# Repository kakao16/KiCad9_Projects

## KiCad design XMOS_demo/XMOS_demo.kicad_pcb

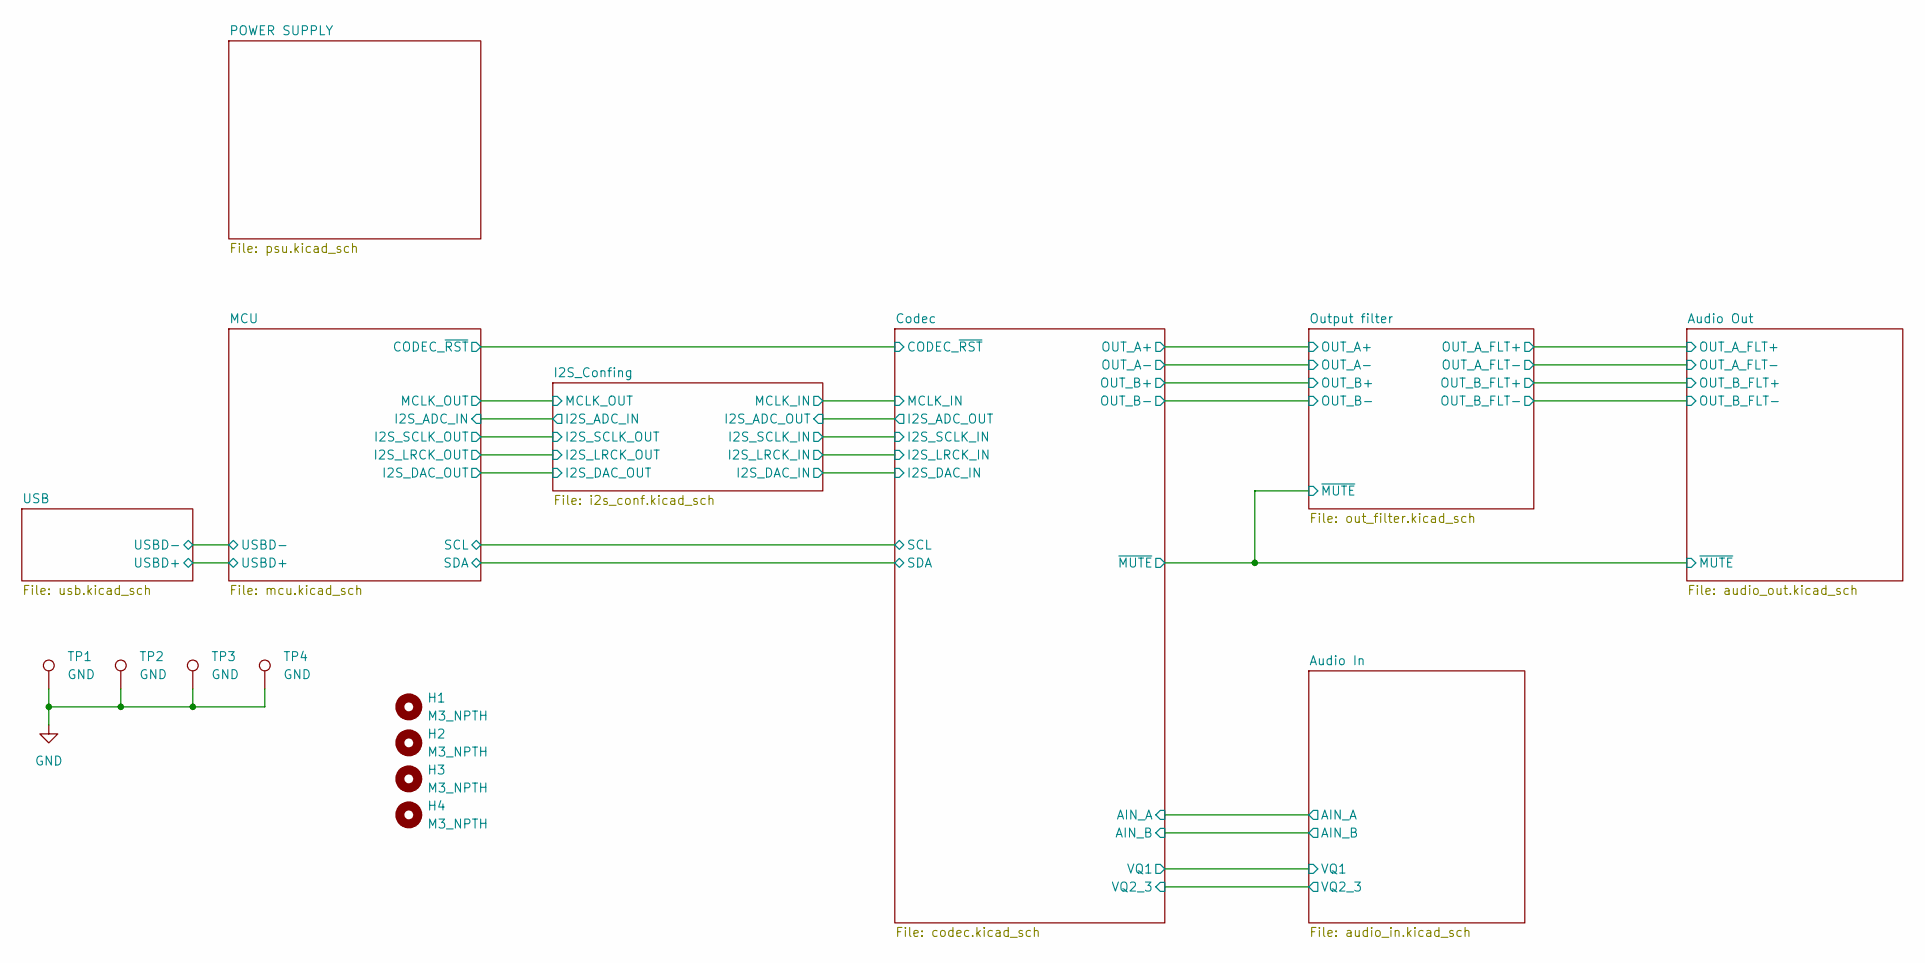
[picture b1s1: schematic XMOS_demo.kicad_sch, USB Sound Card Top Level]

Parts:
H1, H2, H3, H4: M3_NPTH; MountingHole_3.2mm_M3
TP1, TP2, TP3, TP4: GND; TestPoint_Bridge_Pitch2.54mm_Drill1.0mm

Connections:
GND: TP1.1, TP2.1, TP3.1, TP4.1; also elsewhere on the board

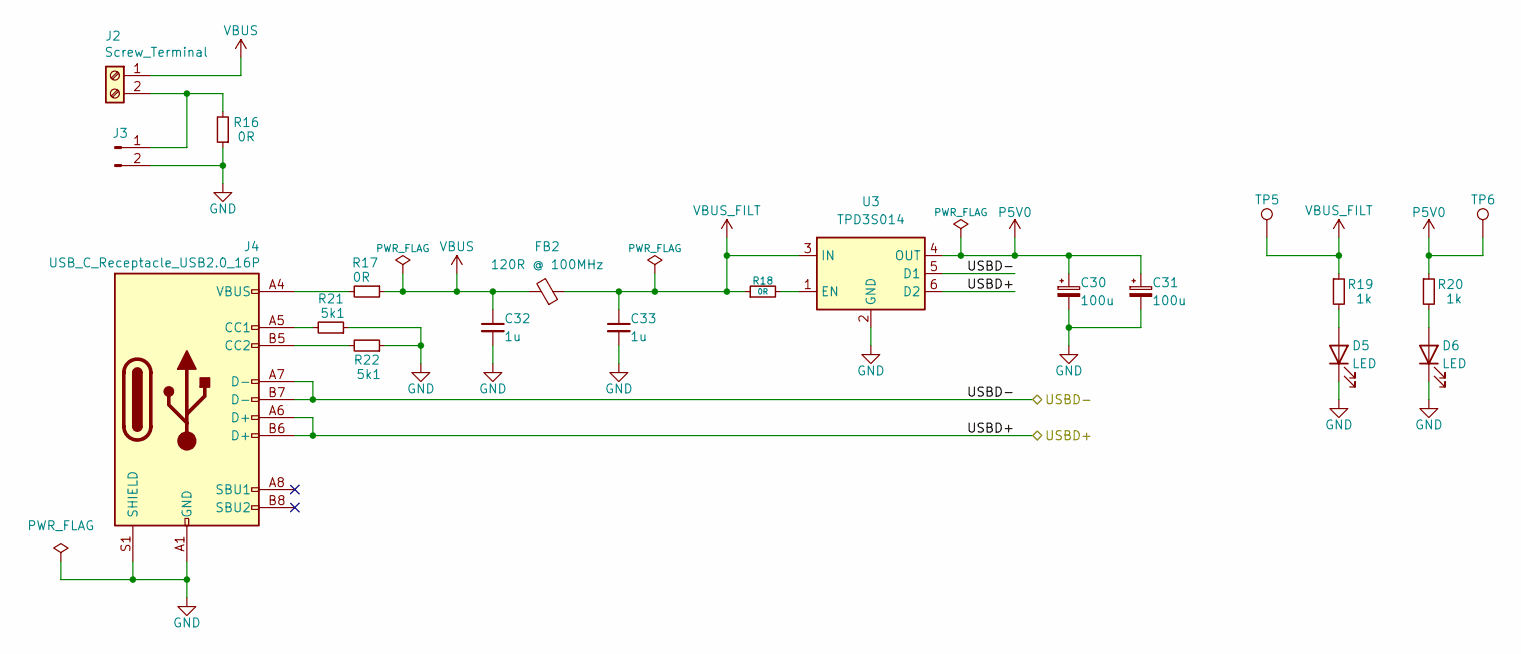
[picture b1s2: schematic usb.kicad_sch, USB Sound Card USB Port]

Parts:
C30, C31: 100u; CP_Elec_6.3x5.7
C32, C33: 1u; C_0603_1608Metric; Max Voltage 16V
D5, D6: LED; LED_0603_1608Metric
FB2: 120R @ 100MHz; L_0603_1608Metric; MPN MI0603M121R-10
J2: Screw_Terminal; TerminalBlock_Phoenix_PT-1,5-2-3.5-H_1x02_P3.50mm_Horizontal
J3: Conn_01x02_Pin; PinHeader_1x02_P2.54mm_Vertical
J4: USB_C_Receptacle_USB2.0_16P; USB_C_Receptacle_GCT_USB4085
R16, R17, R18: 0R; R_0603_1608Metric
R19, R20: 1k; R_0603_1608Metric
R21, R22: 5k1; R_0603_1608Metric
TP5, TP6: TestPoint; TestPoint_Keystone_5005-5009_Compact
U3: TPD3S014; SOT-23-6; MPN TPD3S014DBVR

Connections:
/USB/USBD+: J4.A6 (D+), J4.B6 (D+), U3.6 (D2); also elsewhere on the board
/USB/USBD-: J4.A7 (D-), J4.B7 (D-), U3.5 (D1); also elsewhere on the board
GND: C30.2, C31.2, C32.2, C33.2, D5.1 (K), D6.1 (K), J3.2, J4.A1 (GND), J4.A12 (GND), J4.B1 (GND), J4.B12 (GND), J4.S1 (SHIELD), R16.1, R21.1, R22.1, U3.2 (GND); also elsewhere on the board
unnamed: D5.2 (A), R19.2
unnamed: D6.2 (A), R20.2
unnamed: J2.2, J3.1, R16.2
unnamed: J4.A5 (CC1), R21.2
unnamed: J4.B5 (CC2), R22.2
unnamed: J4.A4 (VBUS), J4.A9 (VBUS), J4.B4 (VBUS), J4.B9 (VBUS), R17.2
unnamed: R18.2, U3.1 (EN)
P5V0: C30.1, C31.1, R20.1, TP6.1, U3.4 (OUT); also elsewhere on the board
VBUS: C32.1, FB2.2, J2.1, R17.1
VBUS_FILT: C33.1, FB2.1, R18.1, R19.1, TP5.1, U3.3 (IN)

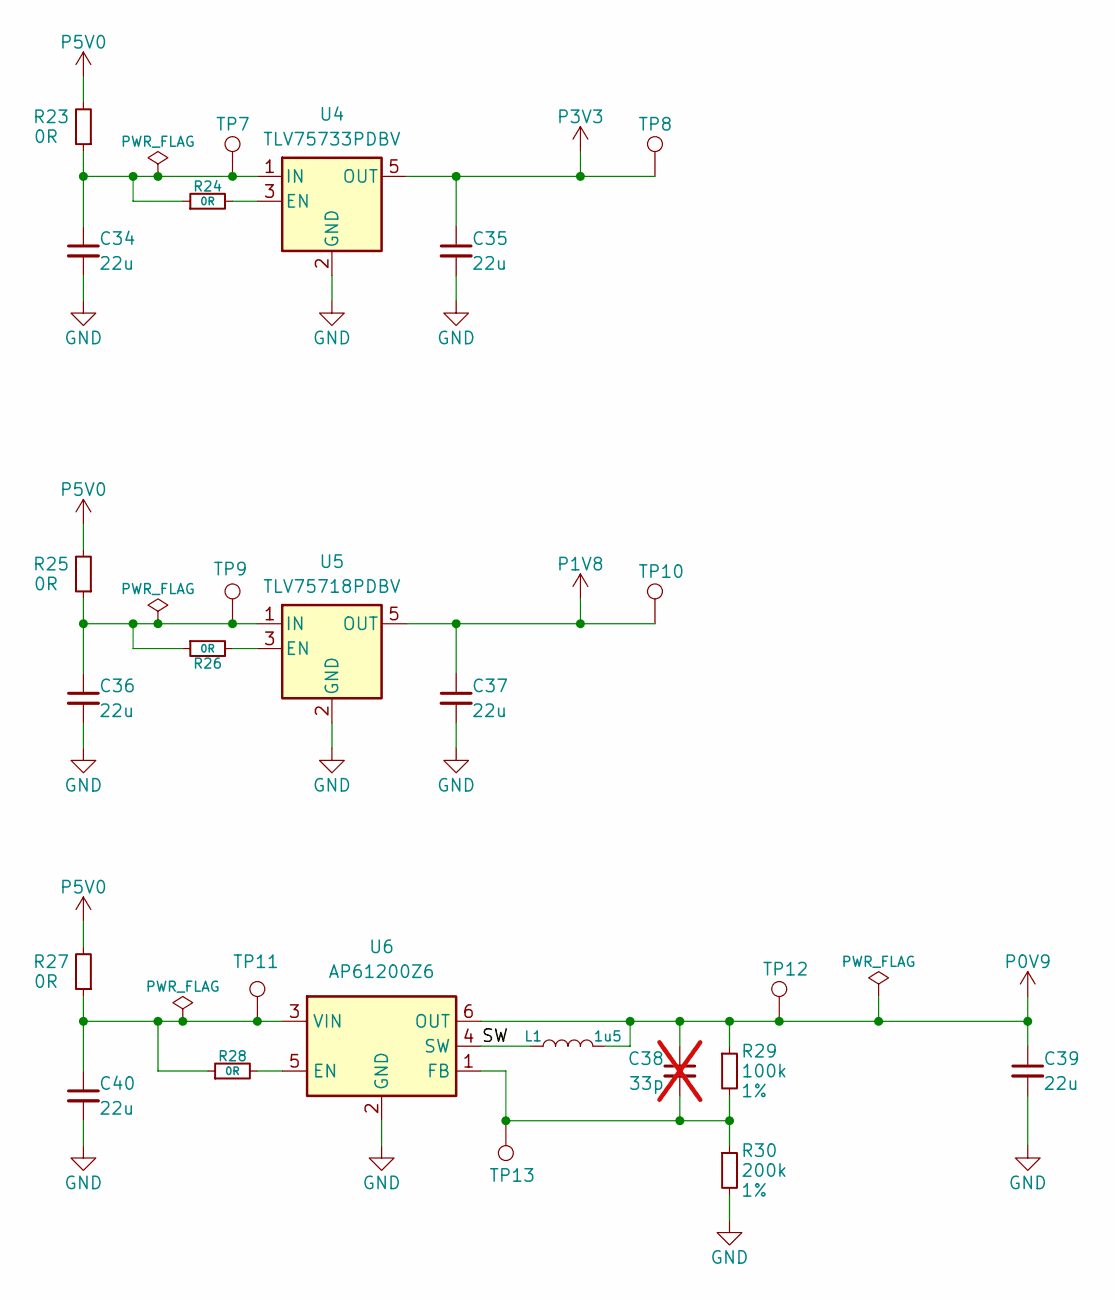
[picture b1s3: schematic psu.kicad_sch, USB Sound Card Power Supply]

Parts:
C34, C35, C36, C37, C40: 22u; C_1206_3216Metric; Max Voltage 16V
C38: 33p; C_0603_1608Metric; Max Voltage 10V; not fitted
C39: 22u; C_0805_2012Metric; Max Voltage 10V
L1: 1u5; L_Abracon_ASPI-3012S_3D_Simple; MPN ASPI-3012S-1R5N-T
R23, R24, R25, R26, R27, R28: 0R; R_0603_1608Metric
R29: 100k; R_0603_1608Metric; Tolerance 1%
R30: 200k; R_0603_1608Metric; Tolerance 1%
TP7, TP9, TP11, TP13: TestPoint; TestPoint_Pad_D2.0mm
TP8, TP10, TP12: TestPoint; TestPoint_Keystone_5005-5009_Compact
U4: TLV75733PDBV; SOT-23-5
U5: TLV75718PDBV; SOT-23-5
U6: AP61200Z6; SOT-563

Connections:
/POWER SUPPLY/SW: L1.1, U6.4 (SW)
GND: C34.2, C35.2, C36.2, C37.2, C39.2, C40.2, R30.2, U4.2 (GND), U5.2 (GND), U6.2 (GND); also elsewhere on the board
unnamed: R24.2, U4.3 (EN)
unnamed: C34.1, R23.1, R24.1, TP7.1, U4.1 (IN)
unnamed: R26.2, U5.3 (EN)
unnamed: C36.1, R25.1, R26.1, TP9.1, U5.1 (IN)
unnamed: R28.2, U6.5 (EN)
unnamed: C38.2, R29.2, R30.1, TP13.1, U6.1 (FB)
unnamed: C40.1, R27.1, R28.1, TP11.1, U6.3 (VIN)
P0V9: C38.1, C39.1, L1.2, R29.1, TP12.1, U6.6 (OUT); also elsewhere on the board
P1V8: C37.1, TP10.1, U5.5 (OUT); also elsewhere on the board
P3V3: C35.1, TP8.1, U4.5 (OUT); also elsewhere on the board
P5V0: R23.2, R25.2, R27.2; also elsewhere on the board

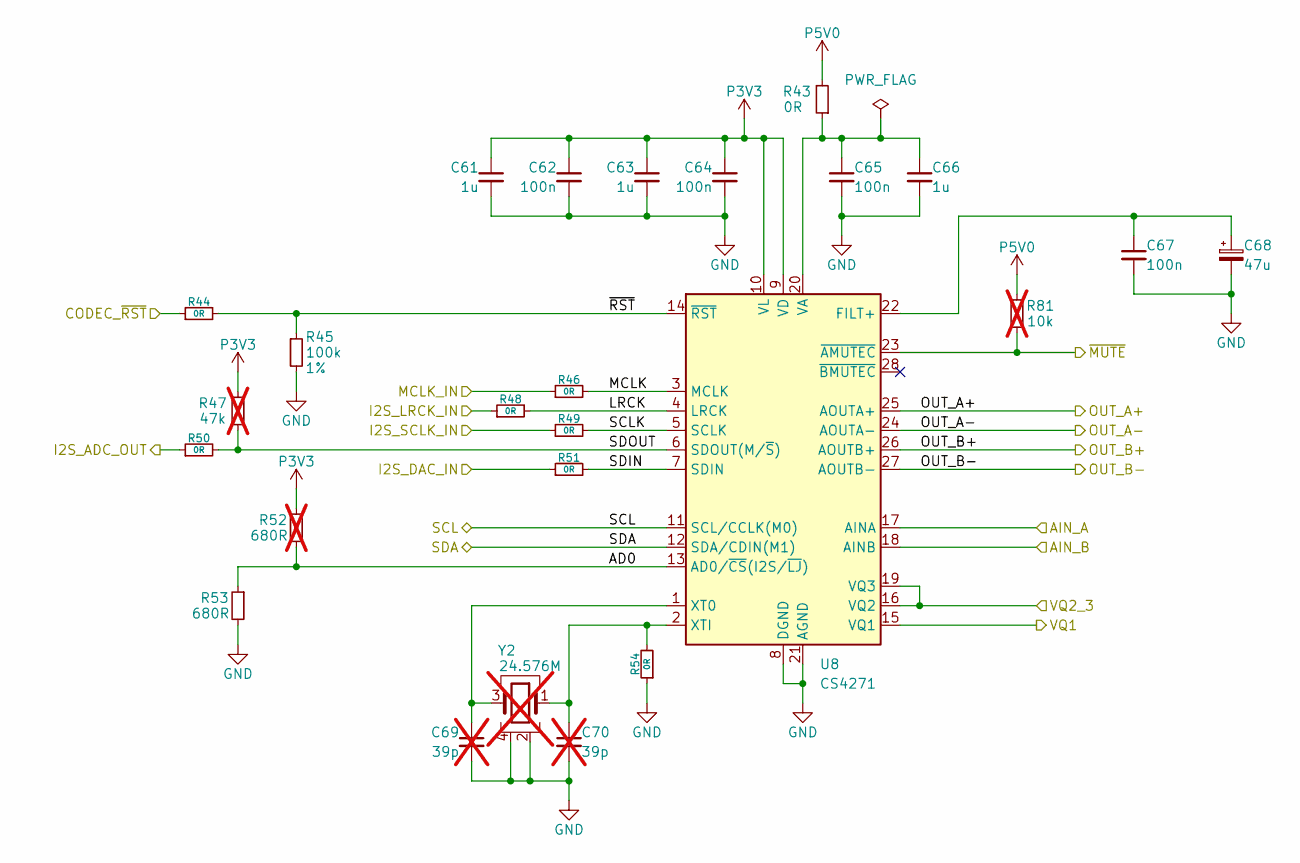
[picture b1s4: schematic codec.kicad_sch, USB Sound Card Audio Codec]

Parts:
C61, C63, C66: 1u; C_0603_1608Metric; Max Voltage 16V
C62, C64, C65: 100n; C_0402_1005Metric; Max Voltage 16V
C67: 100n; C_0603_1608Metric; Max Voltage 16V
C68: 47u; CP_Elec_6.3x5.7
C69, C70: 39p; C_0603_1608Metric; Max Voltage 10V; not fitted
R43, R44, R46, R48, R49, R50, R51, R54: 0R; R_0603_1608Metric
R45: 100k; R_0603_1608Metric; Tolerance 1%
R47: 47k; R_0603_1608Metric; not fitted
R52: 680R; R_0603_1608Metric; not fitted
R53: 680R; R_0603_1608Metric
R81: 10k; R_0603_1608Metric; not fitted
U8: CS4271; TSSOP-28_4.4x9.7mm_P0.65mm
Y2: 24.576M; Crystal_SMD_2520-4Pin_2.5x2.0mm; not fitted

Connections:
/Audio In/AIN_A: U8.17 (AINA); also elsewhere on the board
/Audio In/AIN_B: U8.18 (AINB); also elsewhere on the board
/Audio In/VQ1: U8.15 (VQ1); also elsewhere on the board
/Audio In/VQ2_3: U8.16 (VQ2), U8.19 (VQ3); also elsewhere on the board
/Audio Out/~MUTE: R81.2, U8.23 (~AMUTEC); also elsewhere on the board
/Codec/AD0: R52.2, R53.1, U8.13 (AD0/~CS(I2S/~LJ))
/Codec/I2S_ADC_OUT: R50.1; also elsewhere on the board
/Codec/I2S_DAC_IN: R51.1; also elsewhere on the board
/Codec/I2S_LRCK_IN: R48.1; also elsewhere on the board
/Codec/I2S_SCLK_IN: R49.1; also elsewhere on the board
/Codec/LRCK: R48.2, U8.4 (LRCK)
/Codec/MCLK: R46.2, U8.3 (MCLK)
/Codec/MCLK_IN: R46.1; also elsewhere on the board
/Codec/OUT_A+: U8.25 (AOUTA+); also elsewhere on the board
/Codec/OUT_A-: U8.24 (AOUTA-); also elsewhere on the board
/Codec/OUT_B+: U8.26 (AOUTB+); also elsewhere on the board
/Codec/OUT_B-: U8.27 (AOUTB-); also elsewhere on the board
/Codec/SCL: U8.11 (SCL/CCLK(M0)); also elsewhere on the board
/Codec/SCLK: R49.2, U8.5 (SCLK)
/Codec/SDA: U8.12 (SDA/CDIN(M1)); also elsewhere on the board
/Codec/SDIN: R51.2, U8.7 (SDIN)
/Codec/SDOUT: R47.2, R50.2, U8.6 (SDOUT(M/~S))
/Codec/~RST: R44.2, R45.1, U8.14 (~RST)
/MCU/CODEC_~RST: R44.1; also elsewhere on the board
GND: C61.2, C62.2, C63.2, C64.2, C65.2, C66.2, C67.2, C68.2, C69.2, C70.2, R45.2, R53.2, R54.1, U8.8 (DGND), U8.21 (AGND), Y2.2 (G), Y2.4 (G); also elsewhere on the board
unnamed: C67.1, C68.1, U8.22 (FILT+)
unnamed: C65.1, C66.1, R43.1, U8.20 (VA)
unnamed: C69.1, U8.1 (XT0), Y2.3
unnamed: C70.1, R54.2, U8.2 (XTI), Y2.1
P3V3: C61.1, C62.1, C63.1, C64.1, R47.1, R52.1, U8.9 (VD), U8.10 (VL); also elsewhere on the board
P5V0: R43.2, R81.1; also elsewhere on the board

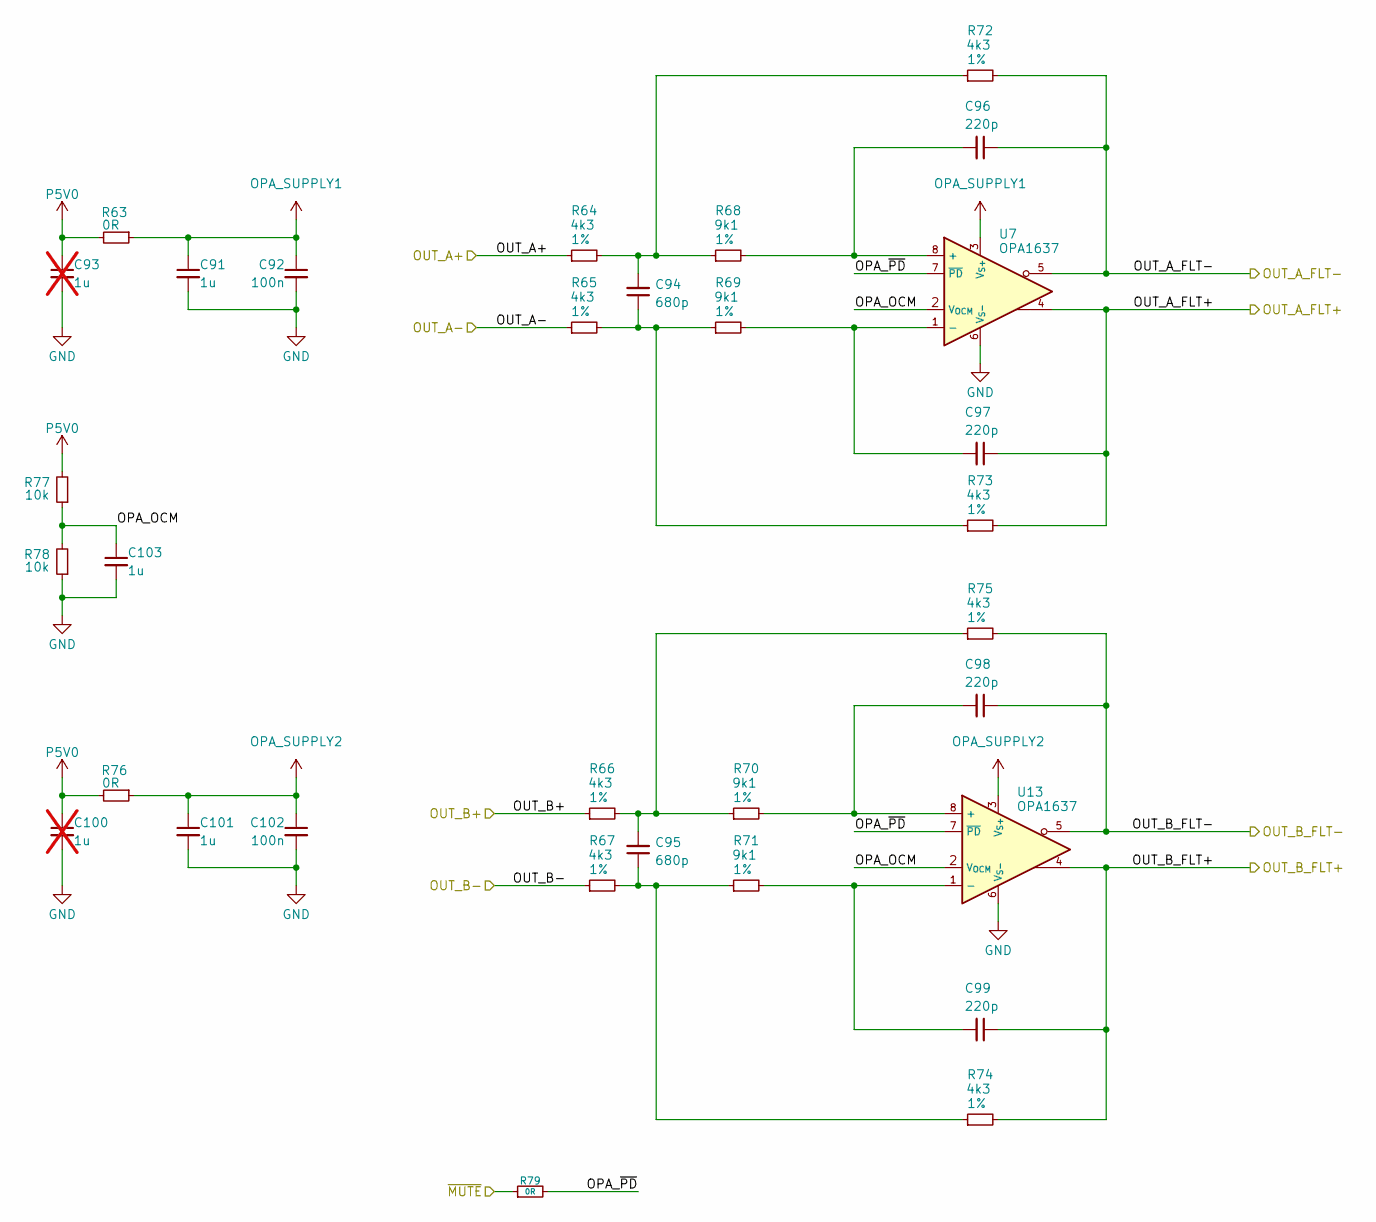
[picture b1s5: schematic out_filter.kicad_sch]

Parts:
C91, C101, C103: 1u; C_0603_1608Metric; Max Voltage 16V
C92, C102: 100n; C_0402_1005Metric; Max Voltage 16V
C93, C100: 1u; C_0603_1608Metric; Max Voltage 16V; not fitted
C94, C95: 680p; C_0603_1608Metric; Max Voltage 25V
C96, C97, C98, C99: 220p; C_0603_1608Metric; Max Voltage 25V
R63, R76, R79: 0R; R_0603_1608Metric
R64, R65, R66, R67, R72, R73, R74, R75: 4k3; R_0603_1608Metric; Tolerance 1%
R68, R69, R70, R71: 9k1; R_0603_1608Metric; Tolerance 1%
R77, R78: 10k; R_0603_1608Metric
U7, U13: OPA1637; VSSOP-8_3x3mm_P0.65mm; MPN OPA1637DGKR

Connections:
/Audio Out/OUT_A_FLT+: C97.1, R73.2, U7.4; also elsewhere on the board
/Audio Out/OUT_A_FLT-: C96.1, R72.2, U7.5; also elsewhere on the board
/Audio Out/OUT_B_FLT+: C99.1, R74.2, U13.4; also elsewhere on the board
/Audio Out/OUT_B_FLT-: C98.1, R75.2, U13.5; also elsewhere on the board
/Audio Out/~MUTE: R79.1; also elsewhere on the board
/Codec/OUT_A+: R64.1; also elsewhere on the board
/Codec/OUT_A-: R65.1; also elsewhere on the board
/Codec/OUT_B+: R66.1; also elsewhere on the board
/Codec/OUT_B-: R67.1; also elsewhere on the board
/Output filter/OPA_OCM: C103.1, R77.1, R78.2, U7.2 (V_{OCM}), U13.2 (V_{OCM})
/Output filter/OPA_~PD: R79.2, U7.7 (~PD), U13.7 (~PD)
GND: C91.2, C92.2, C93.2, C100.2, C101.2, C102.2, C103.2, R78.1, U7.6 (V_{S-}), U13.6 (V_{S-}); also elsewhere on the board
unnamed: C94.1, R65.2, R69.1, R73.1
unnamed: C94.2, R64.2, R68.1, R72.1
unnamed: C95.1, R67.2, R71.1, R74.1
unnamed: C95.2, R66.2, R70.1, R75.1
unnamed: C96.2, R68.2, U7.8 (+)
unnamed: C97.2, R69.2, U7.1 (-)
unnamed: C98.2, R70.2, U13.8 (+)
unnamed: C99.2, R71.2, U13.1 (-)
OPA_SUPPLY1: C91.1, C92.1, R63.1, U7.3 (V_{S+})
OPA_SUPPLY2: C101.1, C102.1, R76.1, U13.3 (V_{S+})
P5V0: C93.1, C100.1, R63.2, R76.2, R77.2; also elsewhere on the board

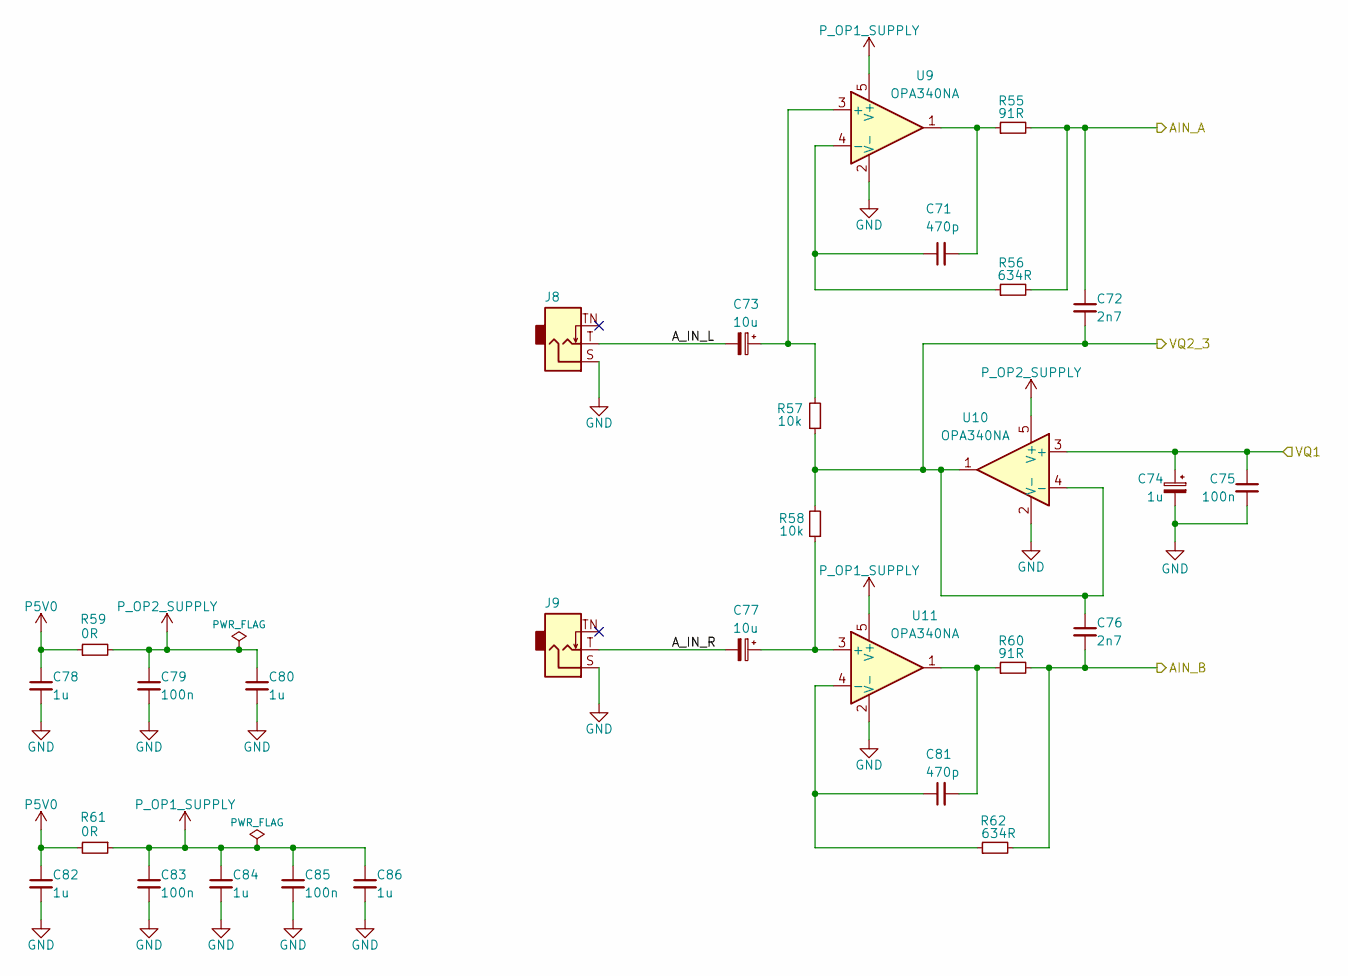
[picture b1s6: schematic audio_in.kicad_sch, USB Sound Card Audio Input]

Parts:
C71, C81: 470p; C_0603_1608Metric; Max Voltage 25V
C72, C76: 2n7; C_0603_1608Metric; Max Voltage 25V
C73, C77: 10u; CP_Elec_4x5.4
C74: 1u; CP_Elec_4x5.4
C75, C79, C83, C85: 100n; C_0603_1608Metric; Max Voltage 16V
C78, C80, C82, C84, C86: 1u; C_0603_1608Metric; Max Voltage 16V
J8, J9: AudioJack2_SwitchT; Jack_3.5mm_CUI_MJ-3523-SMT-TR_Horizontal; MPN MJ-3523-SMT-TR
R55, R60: 91R; R_0603_1608Metric
R56, R62: 634R; R_0603_1608Metric
R57, R58: 10k; R_0603_1608Metric
R59, R61: 0R; R_0603_1608Metric
U9, U10, U11: OPA340NA; SOT-23-5

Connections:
/Audio In/AIN_A: C72.1, R55.2, R56.2; also elsewhere on the board
/Audio In/AIN_B: C76.2, R60.2, R62.2; also elsewhere on the board
/Audio In/A_IN_L: C73.2, J8.T
/Audio In/A_IN_R: C77.2, J9.T
/Audio In/VQ1: C74.1, C75.1, U10.3 (+); also elsewhere on the board
/Audio In/VQ2_3: C72.2, C76.1, R57.1, R58.2, U10.1, U10.4 (-); also elsewhere on the board
GND: C74.2, C75.2, C78.2, C79.2, C80.2, C82.2, C83.2, C84.2, C85.2, C86.2, J8.S, J9.S, U9.2 (V-), U10.2 (V-), U11.2 (V-); also elsewhere on the board
unnamed: C71.2, R55.1, U9.1
unnamed: C81.2, R60.1, U11.1
unnamed: C73.1, R57.2, U9.3 (+)
unnamed: C71.1, R56.1, U9.4 (-)
unnamed: C77.1, R58.1, U11.3 (+)
unnamed: C81.1, R62.1, U11.4 (-)
P5V0: C78.1, C82.1, R59.1, R61.2; also elsewhere on the board
P_OP1_SUPPLY: C83.1, C84.1, C85.1, C86.1, R61.1, U9.5 (V+), U11.5 (V+)
P_OP2_SUPPLY: C79.1, C80.1, R59.2, U10.5 (V+)

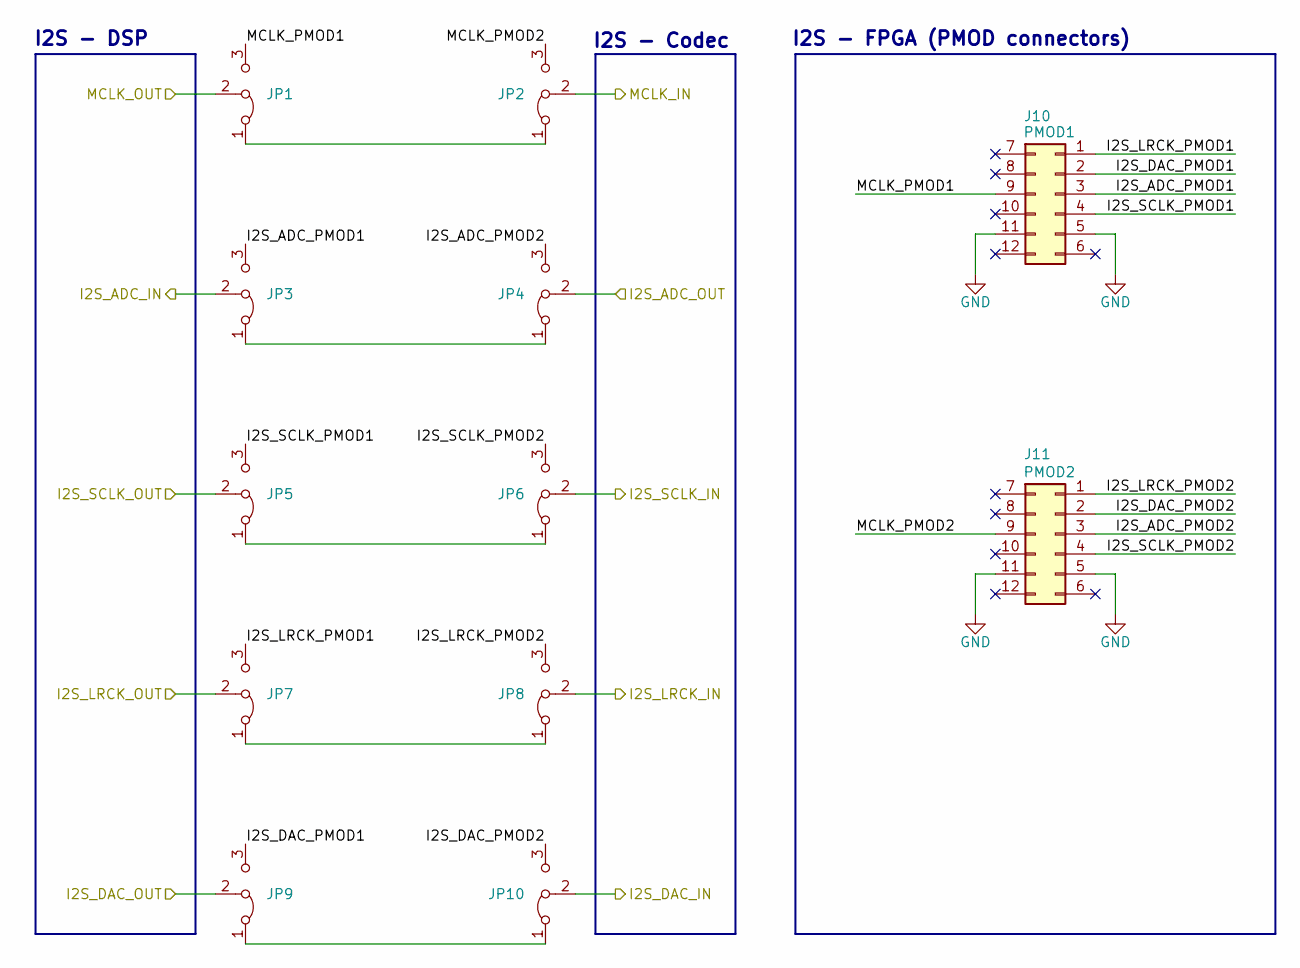
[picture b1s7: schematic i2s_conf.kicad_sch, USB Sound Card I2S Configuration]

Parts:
J10, J11: Conn_PMOD_02x06; PMOD_PinHeader_2x06_P2.54mm_Horizontal
JP1, JP2, JP3, JP4, JP5, JP6, JP7, JP8, JP9, JP10: Jumper_3_Bridged12; PinHeader_1x03_P2.54mm_Vertical

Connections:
/Codec/I2S_ADC_OUT: JP4.2 (C); also elsewhere on the board
/Codec/I2S_DAC_IN: JP10.2 (C); also elsewhere on the board
/Codec/I2S_LRCK_IN: JP8.2 (C); also elsewhere on the board
/Codec/I2S_SCLK_IN: JP6.2 (C); also elsewhere on the board
/Codec/MCLK_IN: JP2.2 (C); also elsewhere on the board
/I2S_Confing/I2S_ADC_PMOD1: J10.3, JP3.3 (B)
/I2S_Confing/I2S_ADC_PMOD2: J11.3, JP4.3 (B)
/I2S_Confing/I2S_DAC_PMOD1: J10.2, JP9.3 (B)
/I2S_Confing/I2S_DAC_PMOD2: J11.2, JP10.3 (B)
/I2S_Confing/I2S_LRCK_PMOD1: J10.1, JP7.3 (B)
/I2S_Confing/I2S_LRCK_PMOD2: J11.1, JP8.3 (B)
/I2S_Confing/I2S_SCLK_PMOD1: J10.4, JP5.3 (B)
/I2S_Confing/I2S_SCLK_PMOD2: J11.4, JP6.3 (B)
/I2S_Confing/MCLK_PMOD1: J10.9, JP1.3 (B)
/I2S_Confing/MCLK_PMOD2: J11.9, JP2.3 (B)
/MCU/I2S_ADC_IN: JP3.2 (C); also elsewhere on the board
/MCU/I2S_DAC_OUT: JP9.2 (C); also elsewhere on the board
/MCU/I2S_LRCK_OUT: JP7.2 (C); also elsewhere on the board
/MCU/I2S_SCLK_OUT: JP5.2 (C); also elsewhere on the board
/MCU/MCLK_OUT: JP1.2 (C); also elsewhere on the board
GND: J10.5, J10.11, J11.5, J11.11; also elsewhere on the board
unnamed: JP1.1 (A), JP2.1 (A)
unnamed: JP3.1 (A), JP4.1 (A)
unnamed: JP5.1 (A), JP6.1 (A)
unnamed: JP7.1 (A), JP8.1 (A)
unnamed: JP9.1 (A), JP10.1 (A)

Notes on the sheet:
I2S - DSP
I2S - FPGA (PMOD connectors)
I2S - Codec

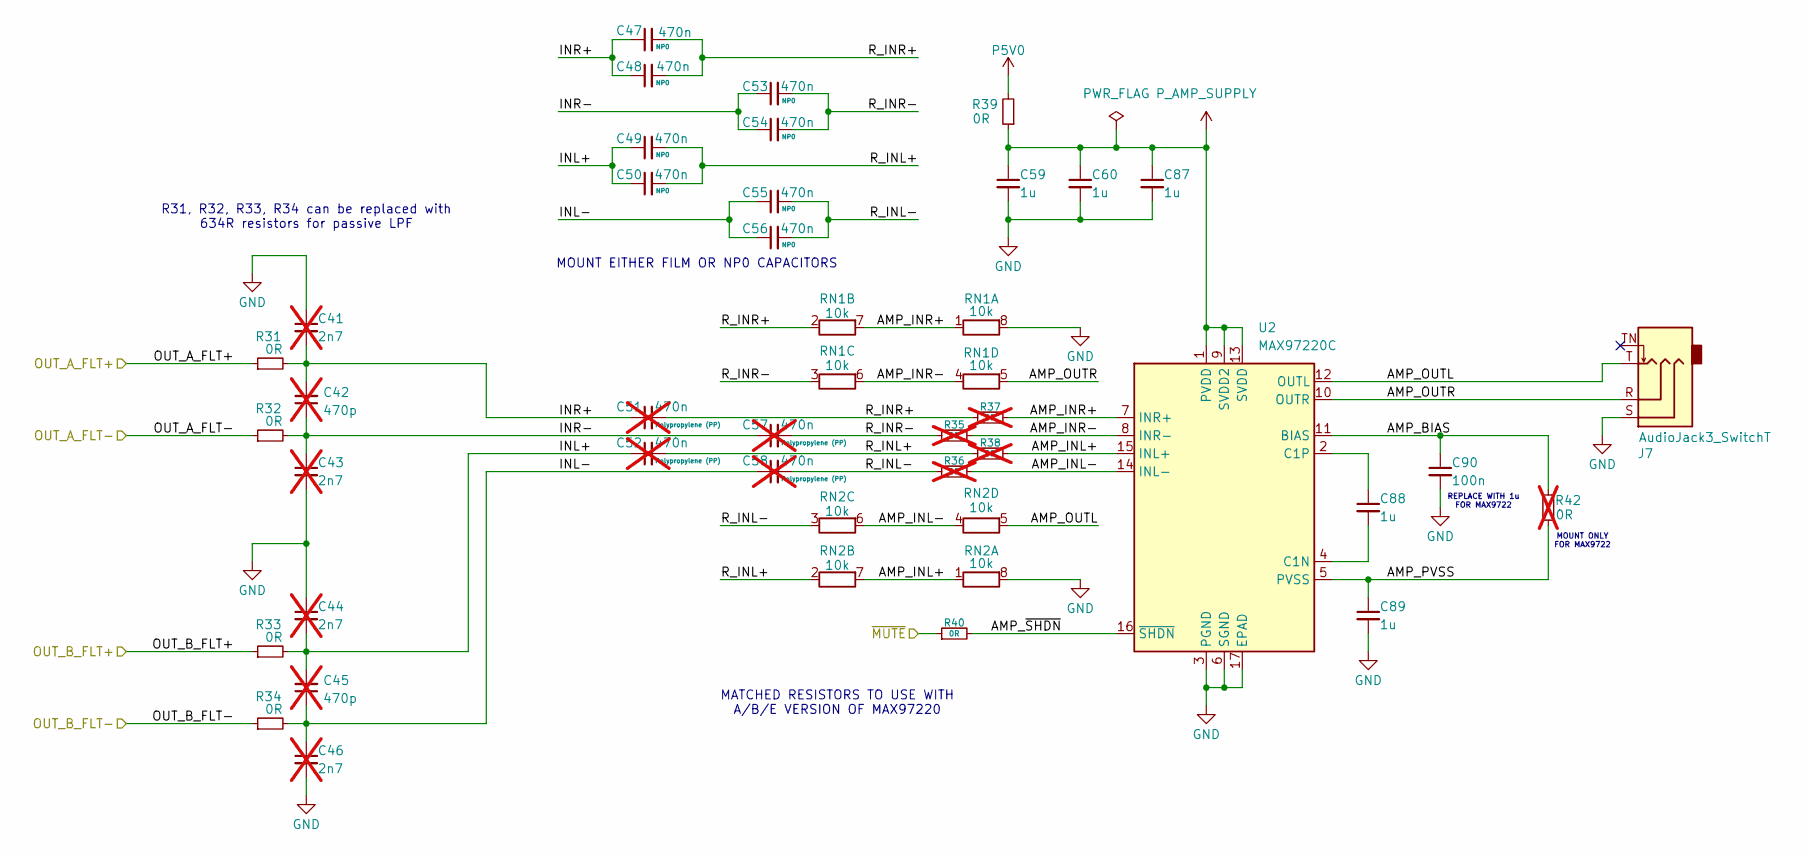
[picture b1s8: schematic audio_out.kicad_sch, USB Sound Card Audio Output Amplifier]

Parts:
C41, C43, C44, C46: 2n7; C_0603_1608Metric; Max Voltage 25V; not fitted
C42, C45: 470p; C_0603_1608Metric; Max Voltage 25V; not fitted
C47, C48, C49, C50, C53, C54, C55, C56: 470n; C_1206_3216Metric_Pad1.33x1.80mm_HandSolder; Max Voltage 25V; MPN GRM31C5C1E474JE01L
C51, C52, C57, C58: 470n; C_Rect_L7.2mm_W8.5mm_P5.00mm_FKP2_FKP2_MKS2_MKP2; Max Voltage DC 100V; MPN MKP2D034701M00KSSD; not fitted
C59, C60, C87, C88, C89: 1u; C_0603_1608Metric; Max Voltage 16V
C90: 100n; C_0402_1005Metric; Max Voltage 16V
J7: AudioJack3_SwitchT; Jack_3.5mm_CUI_SJ-3523-SMT-TR_Horizontal; MPN SJ-3523-SMT-TR
R31, R32, R33, R34, R39, R40: 0R; R_0603_1608Metric
R35, R36, R37, R38, R42: 0R; R_0603_1608Metric; not fitted
RN1, RN2: 10k; R_Array_Convex_4x0603
U2: MAX97220C; TQFN-16-1EP_3x3mm_P0.5mm_EP1.23x1.23mm_ThermalVias

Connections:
/Audio Out/AMP_BIAS: C90.1, R42.2, U2.11 (BIAS)
/Audio Out/AMP_INL+: R38.2, RN2.1 (R1.1), RN2.7 (R2.2), U2.15 (INL+)
/Audio Out/AMP_INL-: R36.2, RN2.4 (R4.1), RN2.6 (R3.2), U2.14 (INL-)
/Audio Out/AMP_INR+: R37.2, RN1.1 (R1.1), RN1.7 (R2.2), U2.7 (INR+)
/Audio Out/AMP_INR-: R35.2, RN1.4 (R4.1), RN1.6 (R3.2), U2.8 (INR-)
/Audio Out/AMP_OUTL: J7.T, RN2.5 (R4.2), U2.12 (OUTL)
/Audio Out/AMP_OUTR: J7.R, RN1.5 (R4.2), U2.10 (OUTR)
/Audio Out/AMP_PVSS: C89.1, R42.1, U2.5 (PVSS)
/Audio Out/AMP_~SHDN: R40.2, U2.16 (~SHDN)
/Audio Out/INL+: C44.2, C45.2, C49.1, C50.1, C52.1, R33.2
/Audio Out/INL-: C45.1, C46.1, C55.1, C56.1, C58.1, R34.2
/Audio Out/INR+: C41.2, C42.2, C47.1, C48.1, C51.1, R31.2
/Audio Out/INR-: C42.1, C43.1, C53.1, C54.1, C57.1, R32.2
/Audio Out/OUT_A_FLT+: R31.1; also elsewhere on the board
/Audio Out/OUT_A_FLT-: R32.1; also elsewhere on the board
/Audio Out/OUT_B_FLT+: R33.1; also elsewhere on the board
/Audio Out/OUT_B_FLT-: R34.1; also elsewhere on the board
/Audio Out/R_INL+: C49.2, C50.2, C52.2, R38.1, RN2.2 (R2.1)
/Audio Out/R_INL-: C55.2, C56.2, C58.2, R36.1, RN2.3 (R3.1)
/Audio Out/R_INR+: C47.2, C48.2, C51.2, R37.1, RN1.2 (R2.1)
/Audio Out/R_INR-: C53.2, C54.2, C57.2, R35.1, RN1.3 (R3.1)
/Audio Out/~MUTE: R40.1; also elsewhere on the board
GND: C41.1, C43.2, C44.1, C46.2, C59.2, C60.2, C87.2, C89.2, C90.2, J7.S, RN1.8 (R1.2), RN2.8 (R1.2), U2.3 (PGND), U2.6 (SGND), U2.17 (EPAD); also elsewhere on the board
unnamed: C88.2, U2.4 (C1N)
unnamed: C88.1, U2.2 (C1P)
P5V0: R39.2; also elsewhere on the board
P_AMP_SUPPLY: C59.1, C60.1, C87.1, R39.1, U2.1 (PVDD), U2.9 (SVDD2), U2.13 (SVDD)

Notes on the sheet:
R31, R32, R33, R34 can be replaced with 634R resistors for passive LPF
MOUNT EITHER FILM OR NP0 CAPACITORS
MOUNT ONLY FOR MAX9722
MATCHED RESISTORS TO USE WITH A/B/E VERSION OF MAX97220
REPLACE WITH 1u FOR MAX9722

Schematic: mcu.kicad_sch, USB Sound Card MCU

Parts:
C1, C2, C3, C4, C5, C6, C7, C8: 100n; C_0402_1005Metric; Max Voltage 16V; not fitted
C9, C10, C11, C12, C13, C14, C15, C16, C17, C18, C19, C20, C21, C22, C23, C25: 100n; C_0402_1005Metric; Max Voltage 16V
C24: 1u; C_0603_1608Metric; Max Voltage 16V
C26, C27: 100n; C_0603_1608Metric; Max Voltage 16V
C28, C29: 18p; C_0402_1005Metric; Max Voltage 10V
D1, D2, D3: LED; LED_0603_1608Metric
D4: SP0505BAHT; SOT-23-6
FB1: 600R @ 100MHz; L_0603_1608Metric; MPN MI0603J601R-10
J1: XSYS2 DEBUG CONNECTOR; IDC-Header_2x10_P1.27mm_Vertical; MPN 20021511-00020T4LF
R1: 5k1; R_0603_1608Metric
R2, R3, R4: 1k; R_0603_1608Metric
R5, R6: 4k7; R_0603_1608Metric
R7, R8: 43R; R_0603_1608Metric
R9, R10, R11, R12, R13: 0R; R_0603_1608Metric
R14: 1M; R_0402_1005Metric
R15: 680R; R_0402_1005Metric
U1: U316-1024-QF60B; QFN-60_7x7mm_P0.4mm_EP_ThermalVias_PowerBars; MPN XU316-1024-QF60B-C24
U12: AT25FF161A; SOIC-8_5.3x5.3mm_P1.27mm; MPN AT25FF161A-SHL-T
Y1: Crystal_24M; Crystal_SMD_2520-4Pin_2.5x2.0mm; MPN STDCSW2-24M

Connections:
/Codec/SCL: R5.2, U1.41 (X0D35); also elsewhere on the board
/Codec/SDA: R6.2, U1.43 (X0D36); also elsewhere on the board
/MCU/CODEC_~RST: U1.11 (X1D09); also elsewhere on the board
/MCU/I2S_ADC_IN: U1.7 (X0D11); also elsewhere on the board
/MCU/I2S_DAC_OUT: U1.9 (X1D00); also elsewhere on the board
/MCU/I2S_LRCK_OUT: U1.10 (X1D01); also elsewhere on the board
/MCU/I2S_SCLK_OUT: U1.13 (X1D10); also elsewhere on the board
/MCU/LED1: R2.1, U1.50 (X0D41)
/MCU/LED2: R3.1, U1.48 (X0D42)
/MCU/LED3: R4.1, U1.46 (X0D40)
/MCU/MCLK_OUT: U1.14 (X1D11); also elsewhere on the board
/MCU/QSPI_CLK: U1.5 (X0D10), U12.6 (CLK)
/MCU/QSPI_D0: U1.59 (X0D04), U12.5 (DI/IO_{0})
/MCU/QSPI_D1: U1.1 (X0D05), U12.2 (DO/IO_{1})
/MCU/QSPI_D2: U1.60 (X0D06), U12.3 (~WP/IO_{2})
/MCU/QSPI_D3: U1.2 (X0D07), U12.7 (~HOLD/~RESET/IO_{3})
/MCU/QSPI_~CS: R1.1, U1.3 (X0D01), U12.1 (~CS)
/MCU/RST_N: R9.2, U1.21 (RST_N)
/MCU/TCK: R10.2, U1.24 (TCK)
/MCU/TDI: R11.2, U1.18 (TDI)
/MCU/TDO: R12.2, U1.20 (TDO)
/MCU/TMS: R13.2, U1.23 (TMS)
/MCU/XL0_IN0: J1.14 (XL_DN0), U1.35 (X1D17)
/MCU/XL0_IN1: J1.12 (XL_DN1), U1.33 (X1D16)
/MCU/XL0_OUT0: J1.16 (XL_UP0), R8.2
/MCU/XL0_OUT1: J1.18 (XL_UP1), R7.2
/MCU/XTAG_RST_N: D4.3 (K), J1.10 (RST_N), R9.1
/MCU/XTAG_TCK: D4.5 (K), J1.4 (TCK), R10.1
/MCU/XTAG_TDI: D4.1 (K), J1.8 (TDI), R11.1
/MCU/XTAG_TDO: D4.6 (K), J1.6 (TDO), R12.1
/MCU/XTAG_TMS: D4.4 (K), J1.2 (TMS), R13.1
/USB/USBD+: U1.29 (USB_DP); also elsewhere on the board
/USB/USBD-: U1.28 (USB_DM); also elsewhere on the board
GND: C1.2, C2.2, C3.2, C4.2, C5.2, C6.2, C7.2, C8.2, C9.2, C10.2, C11.2, C12.2, C13.2, C14.2, C15.2, C16.2, C17.2, C18.2, C19.2, C20.2, C21.2, C22.2, C23.2, C24.2, C25.1, C26.2, C27.2, C28.2, C29.2, D1.1 (K), D2.1 (K), D3.1 (K), D4.2 (A), J1.3 (GND), J1.5 (GND), J1.7 (GND), J1.9 (GND), J1.13 (GND), J1.15 (GND), J1.17 (GND), J1.19 (GND), U1.65 (GND), U12.4 (GND), Y1.2 (G), Y1.4 (G); also elsewhere on the board
unnamed: C29.1, R15.2, Y1.1
unnamed: D1.2 (A), R2.2
unnamed: D2.2 (A), R3.2
unnamed: D3.2 (A), R4.2
unnamed: R7.1, U1.36 (X1D18)
unnamed: R8.1, U1.37 (X1D19)
unnamed: R14.2, R15.1, U1.16 (XIN)
unnamed: C28.1, R14.1, U1.15 (XOUT), Y1.3
P0V9: C1.1, C2.1, C3.1, C4.1, C5.1, C6.1, C7.1, C8.1, C9.1, C10.1, C11.1, C12.1, C13.1, C14.1, C15.1, C16.1, FB1.1, U1.4 (VDD), U1.12 (VDD), U1.19 (VDD), U1.27 (VDD), U1.34 (VDD), U1.42 (VDD), U1.49 (VDD), U1.57 (VDD), U1.61 (VDD), U1.62 (VDD), U1.63 (VDD), U1.64 (VDD); also elsewhere on the board
P0V9A: C24.1, FB1.2, U1.22 (PLL_AVDD)
P1V8: C21.1, C22.1, C23.1, C26.1, J1.1 (VREF_JTAG), U1.17 (VDDIOB18), U1.26 (VDDIOB18), U1.31 (USB_VDD18); also elsewhere on the board
P3V3: C17.1, C18.1, C19.1, C20.1, C25.2, C27.1, J1.11 (VREF_LINK), R1.2, R5.1, R6.1, U1.8 (VDDIOL), U1.30 (USB_VDD33), U1.38 (VDDIOR), U1.52 (VDDIOT), U12.8 (VCC); also elsewhere on the board

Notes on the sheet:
PLACE FOR EXTRA CAPACITORS ON THE BOTTOM OF THE PCB
LOCKED INTO 3V3 FOR IO_L: PLL PIN, CODEC NEEDS 3V3 (3V3 FLASH NEEDED)
